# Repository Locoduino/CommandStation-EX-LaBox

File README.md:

# What is Labox ?

Labox is a projet to build a small DCC Command Station with a dedicated hardware based on ESP32.
The goal is to be able to drive DCC machines, but also use Railcom standard and CAN bus connectivity.
You can find more information on [Locoduino website](https://locoduino.org/).
The software is based on DCC-EX CommandStation software (see below...).

# How to start implementing Labox ?

* Open the file ``CommandStation-EX-LaBox.ino`` in the Arduino IDE or Visual Studio Code (VSC) with PlatformIO extension. Please do not rename the folder containing the sketch code, nor add any files in that folder. The Arduino IDE relies on the structure and name of the folder to properly display and compile the code. 
* Rename or copy ``config.Labox.h`` to ``config.h``. 
* You must edit ``config.h`` according to the help texts in ``config.h``.

# Hardware

Labox is based on a specific PCB designed by Locoduino. The design and gerber files can be found in the 'PCB' folder.

# More information
You can learn more at the [Locoduino website](https://locoduino.org/)

# What is DCC-EX?
DCC-EX is a team of dedicated enthusiasts producing open source DCC & DC solutions for you to run your complete model railroad layout. Our easy to use, do-it-yourself, and free open source products run on off-the-shelf Arduino technology and are supported by numerous third party hardware and apps like JMRI, Engine Driver, wiThrottle, Rocrail and more. 

Currently, our products include the following:

* [EX-CommandStation](https://github.com/DCC-EX/CommandStation-EX/releases)
* [EX-WebThrottle](https://github.com/DCC-EX/exWebThrottle)
* [EX-Installer](https://github.com/DCC-EX/EX-Installer)
* [EX-MotoShield8874](https://dcc-ex.com/reference/hardware/motorboards/ex-motor-shield-8874.html#gsc.tab=0)
* [EX-DCCInspector](https://github.com/DCC-EX/DCCInspector-EX)
* [EX-Toolbox](https://github.com/DCC-EX/EX-Toolbox)
* [EX-Turntable](https://github.com/DCC-EX/EX-Turntable)
* [EX-IOExpander](https://github.com/DCC-EX/EX-IOExpander)
* [EX-FastClock](https://github.com/DCC-EX/EX-FastClock)
* [DCCEXProtocol](https://github.com/DCC-EX/DCCEXProtocol)

Details of these projects can be found on [our web site](https://dcc-ex.com/).

# What’s in this Repository?

This repository, CommandStation-EX, contains a complete DCC-EX *EX-CommmandStation* sketch designed for compiling and uploading into an Arduino Uno, Mega, or Nano.

To utilize this sketch, you can use the following: 

1. (recommended for all levels of user) our [automated installer](https://github.com/DCC-EX/EX-Installer)
2. (intermediate) download the latest version from the [releases page](https://github.com/DCC-EX/CommandStation-EX/releases)
3. (advanced) use git clone on this repository 

Refer to [our web site](https://https://dcc-ex.com/ex-commandstation/get-started/index.html#/) for the hardware required for this project.

**We seriously recommend using the EX-Installer**, however if you choose not to use the installer... 

* Open the file ``CommandStation-EX.ino`` in the Arduino IDE or Visual Studio Code (VSC). Please do not rename the folder containing the sketch code, nor add any files in that folder. The Arduino IDE relies on the structure and name of the folder to properly display and compile the code. 
* Rename or copy ``config.example.h`` to ``config.h``. 
* You must edit ``config.h`` according to the help texts in ``config.h``.

# More information
You can learn more at the [DCC-EX website](https://dcc-ex.com/)

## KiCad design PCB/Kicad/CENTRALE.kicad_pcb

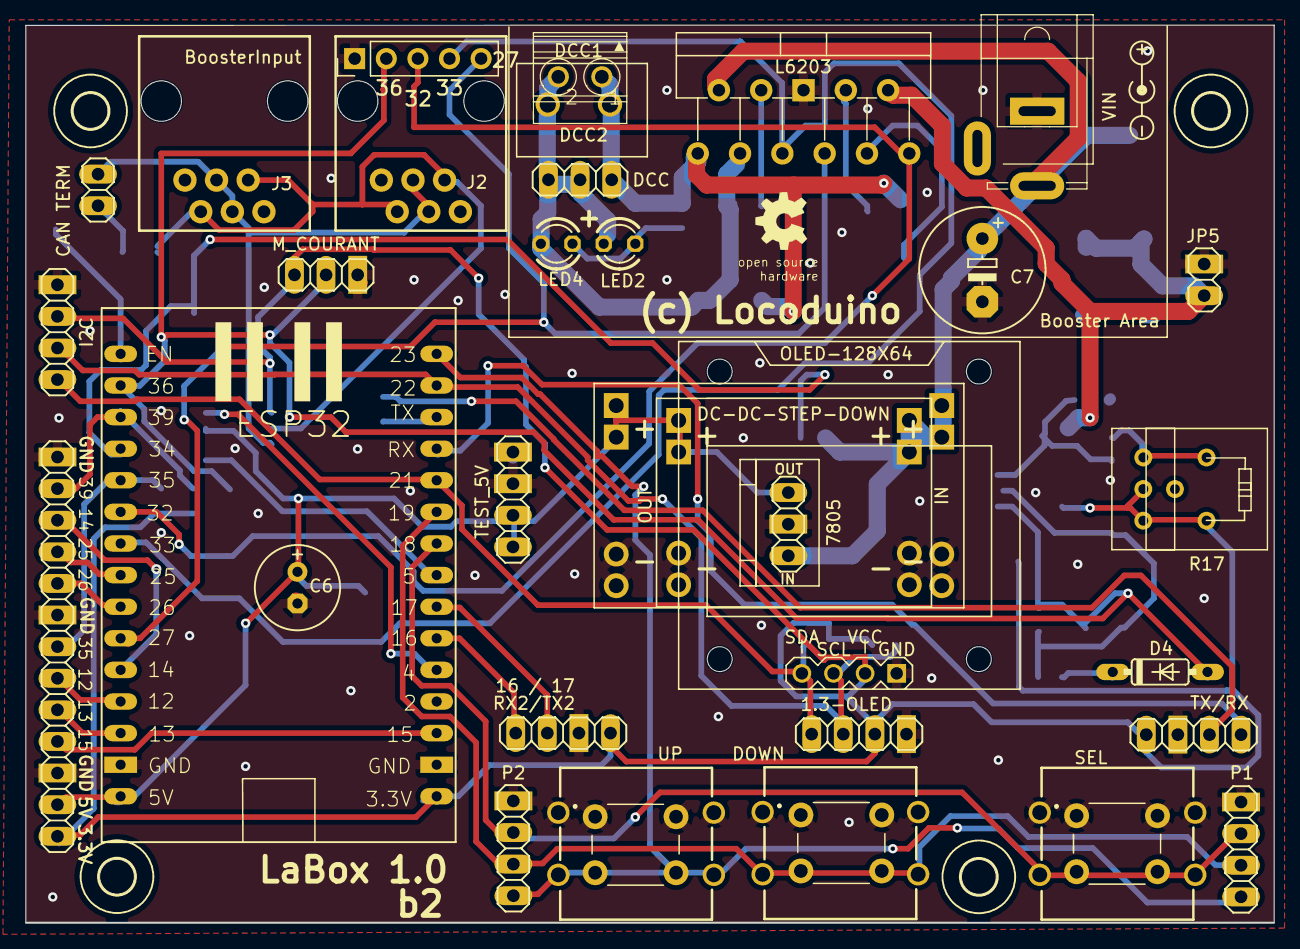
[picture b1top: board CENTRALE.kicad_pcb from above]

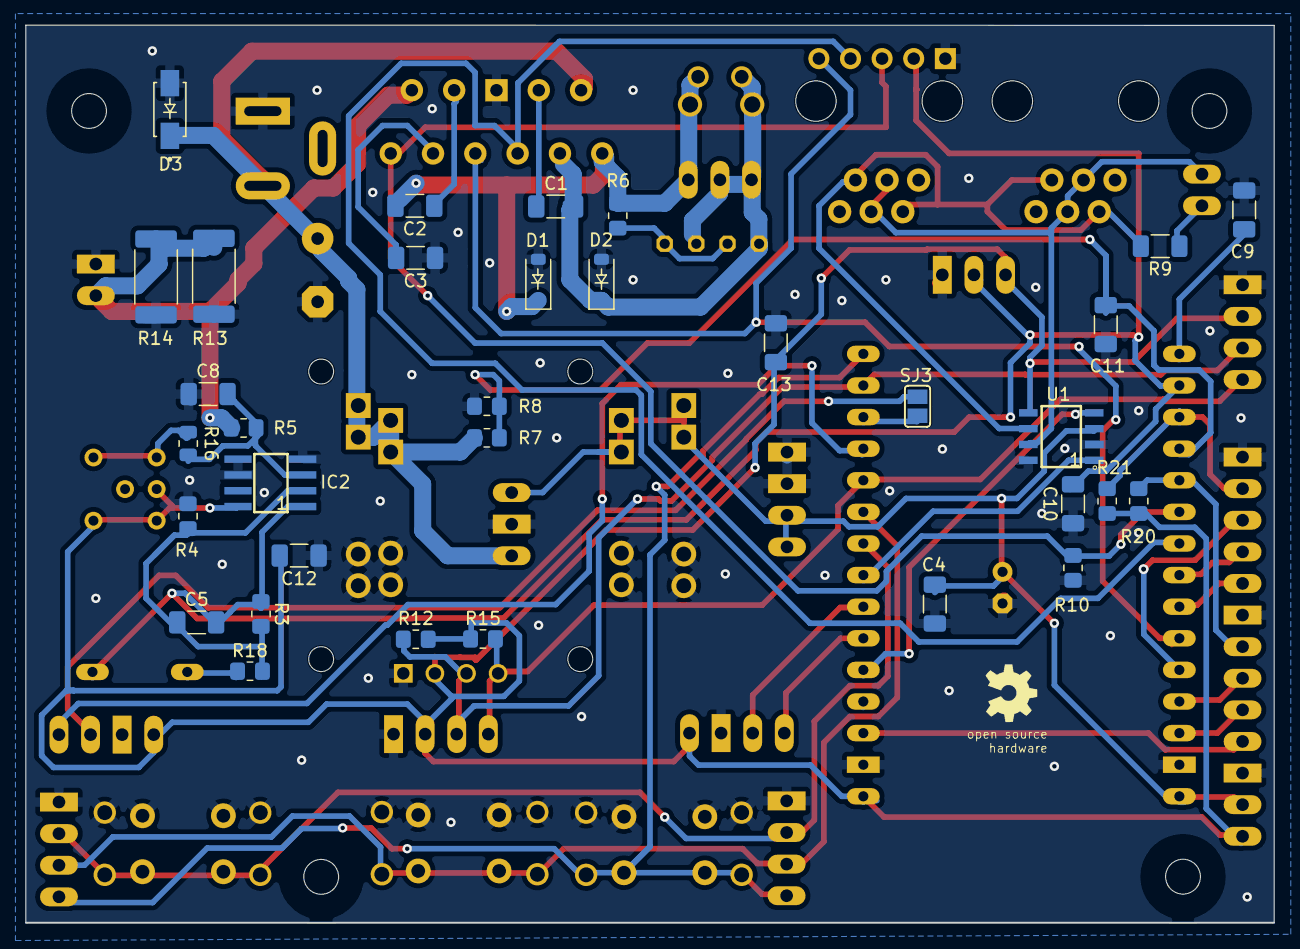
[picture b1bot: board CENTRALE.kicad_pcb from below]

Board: 2 copper layers, 100.3 x 72.1 mm, 75 parts (34 on the bottom side), 44 nets.

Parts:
0.96-OLED: OLED-128X64; DISPLAY-OLED-128X64-I2C
1.3-OLED: 1X04
7805: 1X03
BoosterMode1: BoosterInput; PinHeader_1x05_P2.54mm_Vertical
C1, C2, C4, C5, C8, C10, C11, C12, C13: 100nF; C_1206_3216Metric_Pad1.33x1.80mm_HandSolder
C3: 220nF; C_1206_3216Metric_Pad1.33x1.80mm_HandSolder
C6: 220µF 16V; E2,5-7
C7: 470µ25V; E5-10,5
C9: 470nF; C_1206_3216Metric_Pad1.33x1.80mm_HandSolder
CAN TERM: 1X02
D1, D2: K1N5819HW-7-F; D_SOD-123
D3: SS14; DIOM4325X250N
D4: 1N4148; DO35-7
DCC: 1X03
DCC1: 1751248
DCC2: 691502710002
DOWN: 4304X60737X6
ESP32: ESP32
GOLD_ORB_SM1, GOLD_ORB_SM2: OSHWLOGOLOGO5MM; OSHW_5MM
H1, H2, H3, H4: MOUNT-HOLE2.8; 2,8
I2C: 1X04
IC2: LM358D; SO08
J2, J3: RJ11; RJ11-6
JP1: 1X13
JP5: 1X02
L6203: L6203; TO-220-11_P3.4x5.08mm_StaggerOdd_Lead4.58mm_Vertical
LED2, LED4: LED3MM
M_COURANT: 1X03
P1, P2: 1X04
R3: 0805W8F3302T5E; R_0805_2012Metric_Pad1.20x1.40mm_HandSolder
R4, R5, R6, R8, R10, R12, R15, R18: 0805W8F1002T5E; R_0805_2012Metric_Pad1.20x1.40mm_HandSolder
R7: 0805W8F6802T5E; R_0805_2012Metric_Pad1.20x1.40mm_HandSolder
R9: 1206W4F1200T5E; R_1206_3216Metric_Pad1.30x1.75mm_HandSolder
R13, R14: RLP25FEER500; R_2512_6332Metric_Pad1.40x3.35mm_HandSolder
R16: 0805W8F2203T5E; R_0805_2012Metric
R17: 50k; Potentiometer_Bourns_3386P_Vertical
R20, R21: 0805W8F4702T5E; R_0805_2012Metric_Pad1.20x1.40mm_HandSolder
RX2/TX2: 16/17; 1X04
SEL: 4304X60737X6
SJ3: SJ
SMALL_DOWN: SW_PUSH_6mm_H13mm
SMALL_SEL: SW_PUSH_6mm_H13mm
SMALL_UP: SW_PUSH_6mm_H13mm
TEST_5V: 1X04
TX/RX: 1X04
U1: MCP2562-E/SN; SOIC127P600X175-8N
U$1: DC-DC-STEP-DOWN
U$4: MP1584; DC-DC-STEP-DOWN-MP1584
UP: 4304X60737X6
VIN: SPC4077

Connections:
3V3: 0.96-OLED.2, 1.3-OLED.3, C12.2, C13.2, ESP32.3V3, I2C.2, IC2.8, JP1.1, M_COURANT.1, R12.1, R15.1, R17.3, R20.2, R21.2, RX2/TX2.1, TX/RX.1, U1.5
GND: 0.96-OLED.1, 1.3-OLED.4, 7805.2, BoosterMode1.1, C3.1, C4.2, C6.-, C7.-, C8.1, C9.2, C10.1, C11.1, C12.1, C13.1, D1.2, D2.2, D3.A, DOWN.1, DOWN.2, ESP32.GND, ESP32.GND2, I2C.1, IC2.4, IC2.5, IC2.6, JP1.3, JP1.8, JP1.13, JP5.2, L6203.6, M_COURANT.3, P1.1, P2.1, R4.1, R8.1, R10.1, R13.1, R14.1, RX2/TX2.2, SEL.1, SEL.2, SMALL_DOWN.1, SMALL_SEL.1, SMALL_UP.1, TEST_5V.3, TEST_5V.4, TX/RX.2, U1.2, U1.8, U$1.IN-.1, U$1.IN-.2, U$1.OUT-.1, U$1.OUT-.2, U$4.IN-.1, U$4.IN-.2, U$4.OUT-.1, U$4.OUT-.2, UP.1, UP.2, VIN.1
unnamed: BoosterMode1.5, ESP32.IO27, L6203.7
unnamed: C1.1, L6203.4
unnamed: C2.1, L6203.8
unnamed: ESP32.IO15, JP1.4
unnamed: C2.2, D1.1, DCC.3, DCC1.1, DCC2.1, L6203.1, R6.2
unnamed: C1.2, D2.1, DCC.1, DCC.2, DCC1.2, DCC2.2, L6203.3, LED2.A, LED4.K
unnamed: C5.1, IC2.2, R3.2, R4.2, R18.2
unnamed: C3.2, L6203.9
unnamed: BoosterMode1.2, C5.2, C10.2, D4.A, ESP32.IO36, IC2.1, M_COURANT.2, R3.1
unnamed: JP5.1, L6203.10, R5.1, R13.2, R14.2
unnamed: SJ3.2, TX/RX.3
unnamed: C11.2, ESP32.IO34, R7.1, R8.2
unnamed: 7805.1, C4.1, C6.+, ESP32.5V, JP1.2, TEST_5V.1, TEST_5V.2, U1.3, U$1.OUT+.1, U$1.OUT+.2, U$4.OUT+.1, U$4.OUT+.2
unnamed: C8.2, IC2.3, R5.2, R16.1
unnamed: CAN TERM.2, J2.3, J2.4, J3.3, J3.4, U1.7
unnamed: ESP32.IO5, U1.1
unnamed: BoosterMode1.3, ESP32.IO32, L6203.11, R10.2
unnamed: ESP32.IO13, JP1.5
unnamed: ESP32.IO4, U1.4
unnamed: CAN TERM.1, R9.1
unnamed: ESP32.IO12, JP1.6
unnamed: ESP32.IO23, P1.4, P2.4, SMALL_UP.2, UP.3, UP.4
unnamed: ESP32.IO14, JP1.11
unnamed: ESP32.IO18, P1.2, P2.2, SEL.3, SEL.4, SMALL_SEL.2
unnamed: ESP32.IO26, JP1.9
unnamed: ESP32.IO35, JP1.7, R20.1
unnamed: ESP32.IO39, JP1.12, R21.1
unnamed: 0.96-OLED.4, 1.3-OLED.1, ESP32.IO21, I2C.4, R15.2
unnamed: ESP32.IO25, JP1.10
unnamed: 0.96-OLED.3, 1.3-OLED.2, ESP32.IO22, I2C.3, R12.2
unnamed: BoosterMode1.4, ESP32.IO33, L6203.5
unnamed: R16.2, R17.1
unnamed: ESP32.IO17, RX2/TX2.3
unnamed: D4.C, R18.1
unnamed: LED2.K, LED4.A, R6.1
unnamed: DOWN.3, DOWN.4, ESP32.IO19, P1.3, P2.3, SMALL_DOWN.2
unnamed: J2.2, J2.5, J3.2, J3.5, R9.2, U1.6
unnamed: ESP32.RXD0, TX/RX.4
unnamed: ESP32.TXD0, SJ3.1
unnamed: C9.1, ESP32.EN
unnamed: ESP32.IO16, RX2/TX2.4
VS: 7805.3, C7.+, D3.C, L6203.2, R7.2, U$1.IN+.1, U$1.IN+.2, U$4.IN+.1, U$4.IN+.2, VIN.3

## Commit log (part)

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2022-10-16 First version with DCC output + HMI
2022-11-15 First functionnal version
2022-11-15 First functionnal version 2
2022-11-17 Update README.md
    Change Readme...
2022-11-18 WIfi AP mode working
2023-04-18 First Z21 version
2023-04-22 Working Z21
2023-04-22 Version
2023-05-04 2.2.0 Read CV works !
2023-05-05 Formatting + Auto power On at start for Z21
2023-05-18 2.2.1 Read/Write any CV in prog mode
2023-09-17 2.2.2 Improvements for CV reading
2023-09-20 Base config for Labox.
2023-09-21 Revert "Merge branch 'master' into LaBox"
    This reverts commit 44e6ac6541511a0d5c3dabf24f10aa90de060617, reversing
    changes made to bb87541400e85b9f4c4ef50f9ecfd289e5df2a42.
2023-10-17 CommandStation 5.0 2.2.2
2023-10-21 Fix compil pb
2023-10-21 Fix compil pb 2
2023-10-21 main.yml
2023-10-22 Misc
2023-10-23 Improve UI
2023-10-24 Fix LABOX_PROG_MOTOR_SHIELD
2023-11-07 Fix basic config
2023-11-21 #define HMI_SHOW_CURRENT...
2023-12-01 2.4.0
2023-12-05 deltaCurrent
2023-12-07 Fix USE_HMI
2023-12-07 2.4.1
2023-12-09 Ajout de fonctions pour retour message
2023-12-09 Fix oubli break ligne 78
2023-12-10 Add POWERMODE::OVERLOAD
2024-02-10 2.4.2
2024-02-11 2.4.3
2024-02-18 2.4.4
2024-02-24 2.4.5
2024-02-25 2.4.5 Part II
2024-02-25 2.4.5 Part III
2024-02-25 2.4.5 Fix platforim.IO
2024-03-09 2.4.6
2024-03-10 2.4.7
2024-03-23 LaBox 2.4.7
2024-03-29 Mise en conformité sources.
2024-03-29 0.6.4
2024-08-09 Railcom from lebelge
2024-08-10 2.4.8 Merge with EX master...
2024-08-11 2.5.1
2024-08-11 2.5.1 Part II
2024-08-22 2.4.9
2024-08-22 2.5.2
2024-08-22 2.5.2 II
2024-08-23 2.5.2 III
2024-09-07 2.6.2
2024-09-07 2.6.2 II
2024-09-08 2.6.3
2024-09-08 2.6.3 II
2024-09-08 2.6.3 III
2024-09-14 2.6.4
2024-09-14 2.6.4 II
2024-09-17 2.6.5
2024-09-17 2.6.5 II
2024-09-23 2.6.6
2024-10-08 2.7.0
2024-10-19 2.8.0
2024-10-19 2.8.0 II
2024-10-20 2.8.0 III
2024-11-16 2.9.0
2024-11-16 2.9.0 II
2024-11-16 2.9.0 III
2024-11-24 PCB c3
2025-01-31 PCB 03c4
2025-01-31 2.9.1
2025-01-31 2.9.1 Part II
2025-01-31 PCB 0.3c4 II
2025-05-17 2.10.0
2025-05-17 2.10.0 II
2025-05-18 2.10.0 PCB production files
2025-05-20 2.10.0 PCB Production files II
2025-05-20 2.10.0 III
2025-05-30 PCB 1.0a2
2025-06-15 PCB 1.0a3
2025-06-28 PCB 1.0a4
2025-07-11 PCB 1.0a4 II
2025-07-20 PCB 1.0a5 II
2025-07-20 PCB 1.0a5 III
2025-08-09 PCB 1.0 b0
2025-08-11 PCB 1.00 b0 II
2025-08-25 2.4.11.0
2025-08-25 2.4.11.0 II
2025-10-03 PCB 1.0b1
2025-11-08 PCB 1.0b1 II
2025-11-11 PCB 1.0b1 III
2025-11-21 2.4.12.0
2025-11-21 2.4.12.0 II
2025-11-21 2.4.12.0 III
2025-12-09 2.13.0
2026-03-31 2.14.0
2026-03-31 2.14 II
2026-03-31 2.14.0 III
2026-03-31 2.14.0 IV
2026-04-06 2.15.0
2026-05-24 Remove config.h
